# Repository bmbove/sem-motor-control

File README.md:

# sem-motor-control
See: https://github.com/OSUShellEcoMarathon

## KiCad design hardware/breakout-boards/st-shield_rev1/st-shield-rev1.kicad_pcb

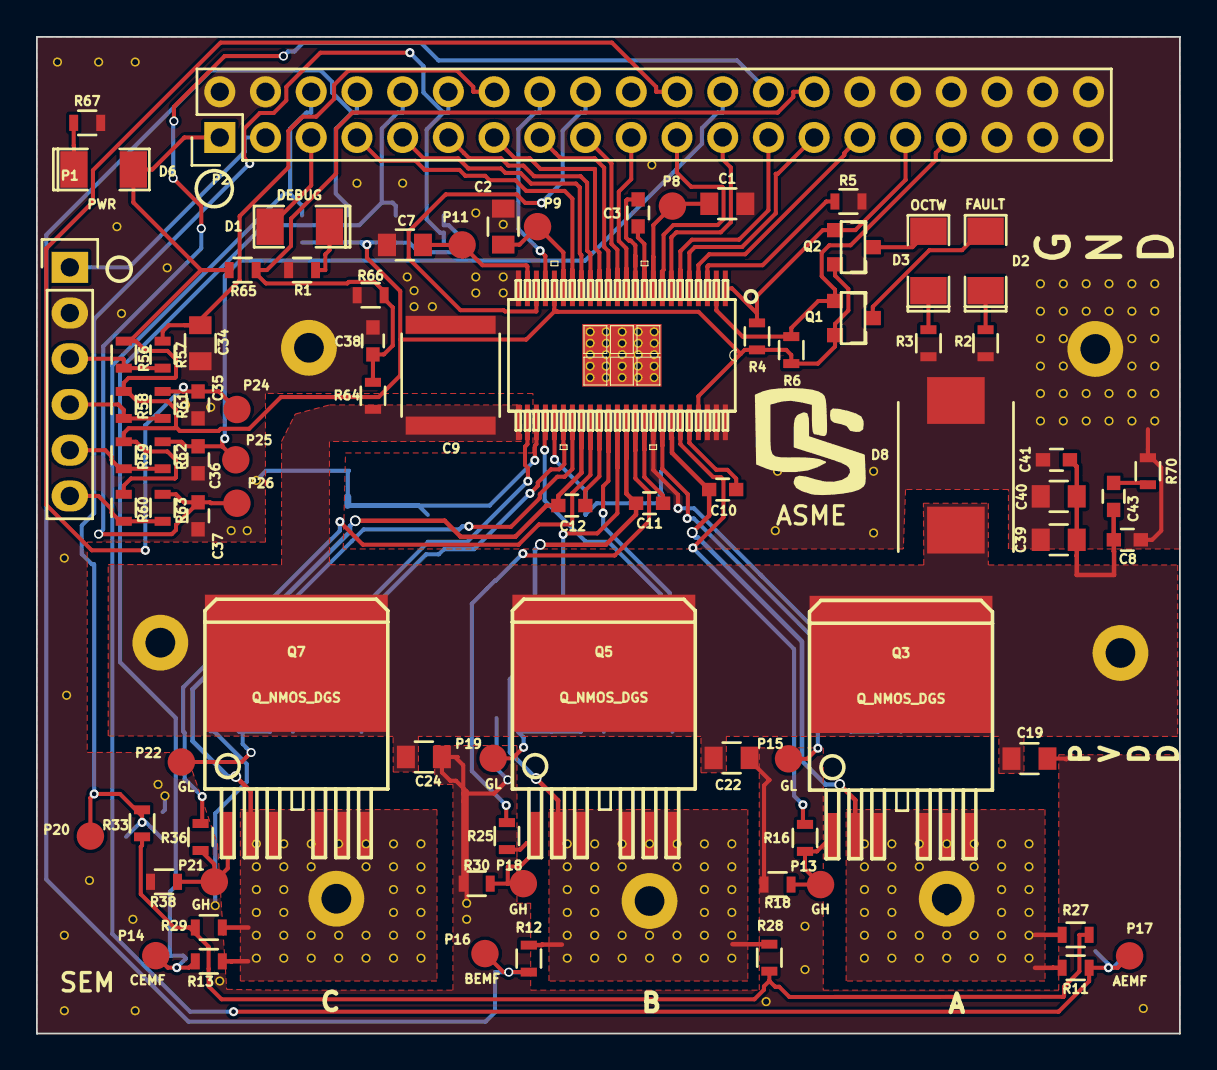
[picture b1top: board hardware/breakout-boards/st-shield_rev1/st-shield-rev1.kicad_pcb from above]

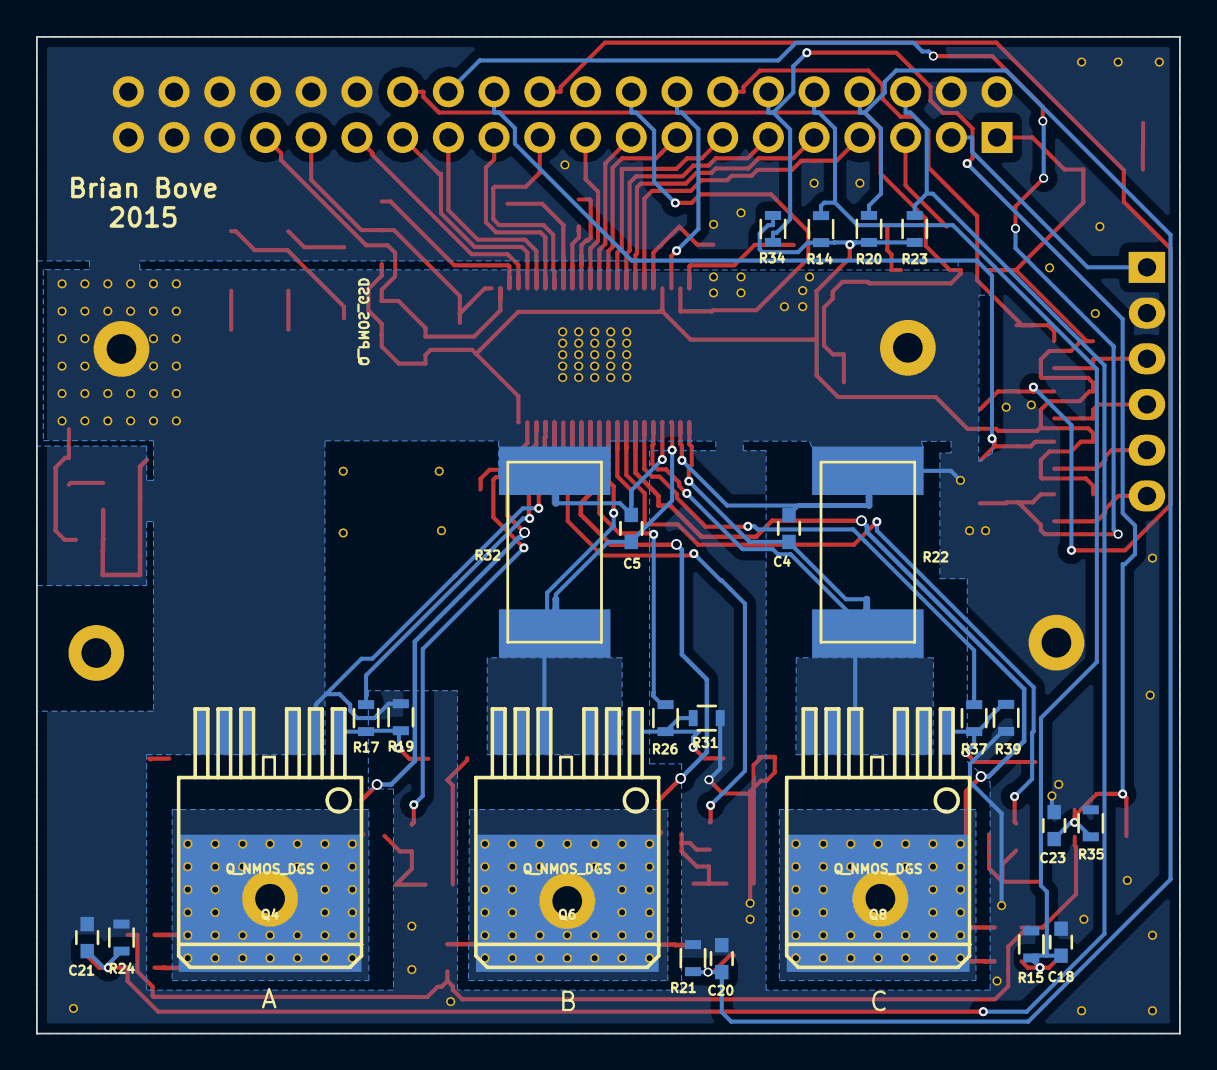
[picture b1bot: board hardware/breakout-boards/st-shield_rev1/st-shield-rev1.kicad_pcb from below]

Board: 2 copper layers, 63.5 x 55.4 mm, 327 parts (29 on the bottom side), 72 nets.

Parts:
C1, C19, C22, C24, C34, C39: 2.2u; C_0805
C2, C7, C40: 1u; C_0805
C3: .022u; C_0603
C4, C5: 1000p; C_0603
C8, C10, C11, C12, C38, C41: .1u; C_0603
C9: 4.7u; C_2220
C18, C20, C21, C23: .001u; C_0603
C35, C36, C37: 100p; C_0603
C43: .01u; C_0603
D1: LED; SMD-1206_Pol
D2: RED; SMD-1206_Pol
D3: YELLOW; SMD-1206_Pol
D6: GREEN; SMD-1206_Pol
D8: TVS; Diode-DO-214AB
MA: hack-via
MB: hack-via
MC: hack-via
P1: CONN_01X06; Pin_Header_Straight_1x06
P2: CONN_02X20; Pin_Header_Straight_2x20
P8, P9, P11, P13, P14, P15, P16, P17, P18, P19, P20, P21, P22, P24, P25, P26: TST; Measurement_Point_Round-SMD-Pad_Small
Q1, Q2: Q_PMOS_GSD; SparkFun-SOT23-3
Q3, Q4, Q5, Q6, Q7, Q8: Q_NMOS_DGS; D2PAK-7
R1, R2, R3, R67: 100; R_0603
R4, R6: 10k; R_0603
R5: 150k; R_0603
R11, R12, R13, R33, R64: 82.5k; R_0603
R14, R20, R23, R34, R65: 30.1k; R_0603
R15, R21, R24, R35, R66: 4.75k; R_0603
R16, R17, R25, R26, R36, R37: 10; R_0603
R18, R19, R30, R31, R38, R39: 47k; R_0603
R22, R32: .0003; WSL3921
R27, R28, R29: 34k; R_0603
R56, R58, R59, R60: 22k; R_0603
R57, R61, R62, R63: 1.6k; R_0603
R70: 3.3; R_0603
U11: DRV8303_DCA_48_SINGLE; drv8303-DCA48_4P42X3P48-M
V1, V2, V3, V4, V111111111, V111111111#2, V111111111#3, V111111111#4, V111111111#5, V111111111#6, V111111111#7, V111111111#8, V111111111#9, V111111111#10, V111111111#11, V111111111#12, V111111111#13, V111111111#14, V111111111#15, V111111111#16, V111111111#17, V111111111#18, V111111111#19, V111111111#20, V111111111#21, V111111111#22, V111111111#23, V111111111#24, V111111111#25, V111111111#26, V111111111#27, V111111111#28, V111111111#29, V111111111#30, V111111111#31, V111111111#32, V111111111#33, V111111111#34, V111111111#35, V111111111#36, V111111111#37, V111111111#38, V111111111#39, V111111111#40, V111111111#41, V111111111#42, V111111111#43, V111111111#44, V111111111#45, V111111111#46, V111111112, V111111113, V111111114, V111111115, V111111121, V111111122, V111111123, V111111124, V111111125, V111111131, V111111132, V111111133, V111111134, V111111135, V111111141, V111111142, V111111143, V111111144, V111111145, V111111151, V111111152, V111111153, V111111154, V111111155, V111111111111, V111111111112, V111111111113, V111111111114, V111111111115, V111111111116, V111111111121, V111111111122, V111111111123, V111111111124, V111111111125, V111111111126, V111111111131, V111111111132, V111111111135, V111111111136, V111111111141, V111111111145, V111111111146, V111111111151, V111111111152, V111111111155, V111111111156, V111111111161, V111111111162, V111111111163, V111111111164, V111111111165, V111111111166, V111111111171, V111111111172, V111111111173, V111111111174, V111111111175, V111111111176, V1111111111111, V1111111111112, V1111111111113, V1111111111114, V1111111111115, V1111111111116, V1111111111121, V1111111111122, V1111111111123, V1111111111124, V1111111111125, V1111111111126, V1111111111131, V1111111111132, V1111111111135, V1111111111136, V1111111111141, V1111111111145, V1111111111146, V1111111111151, V1111111111152, V1111111111155, V1111111111156, V1111111111161, V1111111111162, V1111111111163, V1111111111164, V1111111111165, V1111111111166, V1111111111171, V1111111111172, V1111111111173, V1111111111174, V1111111111175, V1111111111176, V11111111111111, V11111111111112, V11111111111113, V11111111111114, V11111111111115, V11111111111116, V11111111111121, V11111111111122, V11111111111123, V11111111111124, V11111111111125, V11111111111126, V11111111111131, V11111111111132, V11111111111135, V11111111111136, V11111111111141, V11111111111143, V11111111111144, V11111111111145, V11111111111146, V11111111111151, V11111111111152, V11111111111155, V11111111111156, V11111111111161, V11111111111162, V11111111111163, V11111111111164, V11111111111165, V11111111111166, V11111111111171, V11111111111172, V11111111111173, V11111111111174, V11111111111175, V11111111111176, V1111111111111111, V1111111111111112, V1111111111111113, V1111111111111114, V1111111111111115, V1111111111111116, V1111111111111121, V1111111111111122, V1111111111111123, V1111111111111124, V1111111111111125, V1111111111111126, V1111111111111131, V1111111111111132, V1111111111111135, V1111111111111136, V1111111111111141, V1111111111111142, V1111111111111145, V1111111111111146, V1111111111111151, V1111111111111152, V1111111111111153, V1111111111111154, V1111111111111155, V1111111111111156, V1111111111111161, V1111111111111162, V1111111111111163, V1111111111111164, V1111111111111165, V1111111111111166: hack-via
W1, W2, W3, W4: NET-TIE; nettie

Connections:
3V3: D6.2, P2.1, Q1.2, Q2.2, R4.1, R6.1, R14.1, R20.1, R23.1, R34.1, R56.1, R58.1, R59.1, R60.1, R65.1, U11.20, U11.45
5V: P1.1, P2.3
/FET Driver/DC_CAL: P2.21, U11.8
/FET Driver/EN: P2.19, U11.12
/FET Driver/FAULT: P2.33, Q1.1, R6.2, U11.2
/FET Driver/INH_A: P2.17, U11.13
/FET Driver/INH_B: P2.13, U11.15
/FET Driver/INH_C: P2.9, U11.17
/FET Driver/INL_A: P2.15, U11.14
/FET Driver/INL_B: P2.11, U11.16
/FET Driver/INL_C: P2.7, U11.18
/FET Driver/OCTW: P2.31, Q2.1, R4.2, U11.1
/FET Driver/SCLK: P2.23, U11.7
/FET Driver/SCS: P2.29, U11.4
/FET Driver/SDI: P2.27, U11.5
/FET Driver/SDO: P2.25, U11.6
/FET Driver/SL_B: Q6.3, R32.2, U11.35, W3.1
/FET Driver/SL_C: Q8.3, R22.2, U11.30, W1.1
/FET Driver/SO1: P2.16, U11.21
/FET Driver/SO2: P2.18, U11.22
/Hall Effect Sensor Filters/HALL_A_IN: P1.4, R58.2, R61.2
/Hall Effect Sensor Filters/HALL_A_OUT: C35.1, P2.22, P24.1, R61.1
/Hall Effect Sensor Filters/HALL_B_IN: P1.5, R59.2, R62.2
/Hall Effect Sensor Filters/HALL_B_OUT: C36.1, P2.24, P25.1, R62.1
/Hall Effect Sensor Filters/HALL_C_IN: P1.6, R60.2, R63.2
/Hall Effect Sensor Filters/HALL_C_OUT: C37.1, P2.26, P26.1, R63.1
/LED_D: D1.2, P2.5
/MOSFET Array/AEMF: C21.1, P2.6, P17.1, R11.1, R23.2, R24.1
/MOSFET Array/A_HI: R16.2, U11.43
/MOSFET Array/A_LO: R17.2, U11.41
/MOSFET Array/BEMF: C20.1, P2.8, P16.1, R12.1, R20.2, R21.1
/MOSFET Array/B_HI: R25.2, U11.38
/MOSFET Array/B_LO: R26.2, U11.36
/MOSFET Array/CEMF: C18.1, P2.10, P14.1, R13.1, R14.2, R15.1
/MOSFET Array/CUR_BN: C5.2, U11.29, W4.2
/MOSFET Array/CUR_BP: C5.1, U11.28, W3.2
/MOSFET Array/CUR_CN: C4.2, U11.27, W2.2
/MOSFET Array/CUR_CP: C4.1, U11.26, W1.2
/MOSFET Array/C_HI: R36.2, U11.33
/MOSFET Array/C_LO: R37.2, U11.31
/MOSFET Array/MOTOR_A: C10.2, Q3.3, Q4.1, R11.2, R27.2, U11.42, V11111111111111.1, V11111111111112.1, V11111111111113.1, V11111111111114.1, V11111111111115.1, V11111111111116.1, V11111111111121.1, V11111111111122.1, V11111111111123.1, V11111111111124.1, V11111111111125.1, V11111111111126.1, V11111111111131.1, V11111111111132.1, V11111111111135.1, V11111111111136.1, V11111111111141.1, V11111111111143.1, V11111111111144.1, V11111111111145.1, V11111111111146.1, V11111111111151.1, V11111111111152.1, V11111111111155.1, V11111111111156.1, V11111111111161.1, V11111111111162.1, V11111111111163.1, V11111111111164.1, V11111111111165.1, V11111111111166.1, V11111111111171.1, V11111111111172.1, V11111111111173.1, V11111111111174.1, V11111111111175.1, V11111111111176.1
/MOSFET Array/MOTOR_B: C11.2, Q5.3, Q6.1, R12.2, R28.2, U11.37, V1111111111111.1, V1111111111112.1, V1111111111113.1, V1111111111114.1, V1111111111115.1, V1111111111116.1, V1111111111121.1, V1111111111122.1, V1111111111123.1, V1111111111124.1, V1111111111125.1, V1111111111126.1, V1111111111131.1, V1111111111132.1, V1111111111135.1, V1111111111136.1, V1111111111141.1, V1111111111145.1, V1111111111146.1, V1111111111151.1, V1111111111152.1, V1111111111155.1, V1111111111156.1, V1111111111161.1, V1111111111162.1, V1111111111163.1, V1111111111164.1, V1111111111165.1, V1111111111166.1, V1111111111171.1, V1111111111172.1, V1111111111173.1, V1111111111174.1, V1111111111175.1, V1111111111176.1
/MOSFET Array/MOTOR_C: C12.2, Q7.3, Q8.1, R13.2, R29.2, U11.32, V111111111111.1, V111111111112.1, V111111111113.1, V111111111114.1, V111111111115.1, V111111111116.1, V111111111121.1, V111111111122.1, V111111111123.1, V111111111124.1, V111111111125.1, V111111111126.1, V111111111131.1, V111111111132.1, V111111111135.1, V111111111136.1, V111111111141.1, V111111111145.1, V111111111146.1, V111111111151.1, V111111111152.1, V111111111155.1, V111111111156.1, V111111111161.1, V111111111162.1, V111111111163.1, V111111111164.1, V111111111165.1, V111111111166.1, V111111111171.1, V111111111172.1, V111111111173.1, V111111111174.1, V111111111175.1, V111111111176.1
/MOSFET Array/MOTOR_N: C23.1, P2.12, P20.1, R33.1, R34.2, R35.1
/Power Management/DC_IN: C38.1, P2.28, R64.1, R65.2, R66.1
/Temperature Sensors/T0: C34.1, P2.14, R57.1
/Temperature Sensors/T_MOTOR: P1.3, R56.2, R57.2
GND: C1.2, C2.2, C7.2, C8.2, C9.2, C18.2, C19.2, C20.2, C21.2, C22.2, C23.2, C24.2, C34.2, C35.2, C36.2, C37.2, C38.2, C39.2, C40.2, C41.2, D8.2, P1.2, P2.2, P2.4, P2.30, P2.32, P2.34, P2.35, P2.36, P2.37, P2.38, P2.39, P2.40, Q4.3, R1.2, R2.2, R3.2, R5.2, R15.2, R18.1, R19.1, R21.2, R22.1, R24.2, R30.1, R31.1, R32.1, R35.2, R38.1, R39.1, R66.2, R67.2, R70.2, U11.24, U11.40, U11.46, U11.47, U11.48, V111111111.1, V111111111#2.1, V111111111#3.1, V111111111#4.1, V111111111#5.1, V111111111#6.1, V111111111#7.1, V111111111#8.1, V111111111#9.1, V111111111#10.1, V111111111#11.1, V111111111#12.1, V111111111#13.1, V111111111#14.1, V111111111#15.1, V111111111#16.1, V111111111#17.1, V111111111#18.1, V111111111#19.1, V111111111#20.1, V111111111#21.1, V111111111#22.1, V111111111#23.1, V111111111#24.1, V111111111#25.1, V111111111#26.1, V111111111#27.1, V111111111#28.1, V111111111#29.1, V111111111#30.1, V111111111#31.1, V111111111#32.1, V111111111#33.1, V111111111#34.1, V111111111#35.1, V111111111#36.1, V111111111#37.1, V111111111#38.1, V111111111#39.1, V111111111#40.1, V111111111#41.1, V111111111#42.1, V111111111#43.1, V111111111#44.1, V111111111#45.1, V111111111#46.1, V111111112.1, V111111113.1, V111111114.1, V111111115.1, V111111121.1, V111111122.1, V111111123.1, V111111124.1, V111111125.1, V111111131.1, V111111132.1, V111111133.1, V111111134.1, V111111135.1, V111111141.1, V111111142.1, V111111143.1, V111111144.1, V111111145.1, V111111151.1, V111111152.1, V111111153.1, V111111154.1, V111111155.1, V1111111111111111.1, V1111111111111112.1, V1111111111111113.1, V1111111111111114.1, V1111111111111115.1, V1111111111111116.1, V1111111111111121.1, V1111111111111122.1, V1111111111111123.1, V1111111111111124.1, V1111111111111125.1, V1111111111111126.1, V1111111111111131.1, V1111111111111132.1, V1111111111111135.1, V1111111111111136.1, V1111111111111141.1, V1111111111111142.1, V1111111111111145.1, V1111111111111146.1, V1111111111111151.1, V1111111111111152.1, V1111111111111153.1, V1111111111111154.1, V1111111111111155.1, V1111111111111156.1, V1111111111111161.1, V1111111111111162.1, V1111111111111163.1, V1111111111111164.1, V1111111111111165.1, V1111111111111166.1, W2.1, W4.1
unnamed: C1.1, P8.1, U11.9
unnamed: C2.1, P9.1, U11.19
unnamed: C3.1, U11.10
unnamed: C3.2, U11.11
unnamed: C7.1, P11.1, U11.23
unnamed: C10.1, U11.44
unnamed: C11.1, U11.39
unnamed: C12.1, U11.34
unnamed: C43.2, R70.1
unnamed: D1.1, R1.1
unnamed: D2.1, R2.1
unnamed: D2.2, Q1.3
unnamed: D3.1, R3.1
unnamed: D3.2, Q2.3
unnamed: D6.1, R67.1
unnamed: P13.1, Q3.2, R16.1, R18.2
unnamed: P15.1, Q4.2, R17.1, R19.2
unnamed: P18.1, Q5.2, R25.1, R30.2
unnamed: P19.1, Q6.2, R26.1, R31.2
unnamed: P21.1, Q7.2, R36.1, R38.2
unnamed: P22.1, Q8.2, R37.1, R39.2
unnamed: R5.1, U11.3
unnamed: R27.1, R28.1, R29.1, R33.2
PVDD: C8.1, C9.1, C19.1, C22.1, C24.1, C39.1, C40.1, C41.1, C43.1, D8.1, Q3.1, Q5.1, Q7.1, R64.2, U11.25

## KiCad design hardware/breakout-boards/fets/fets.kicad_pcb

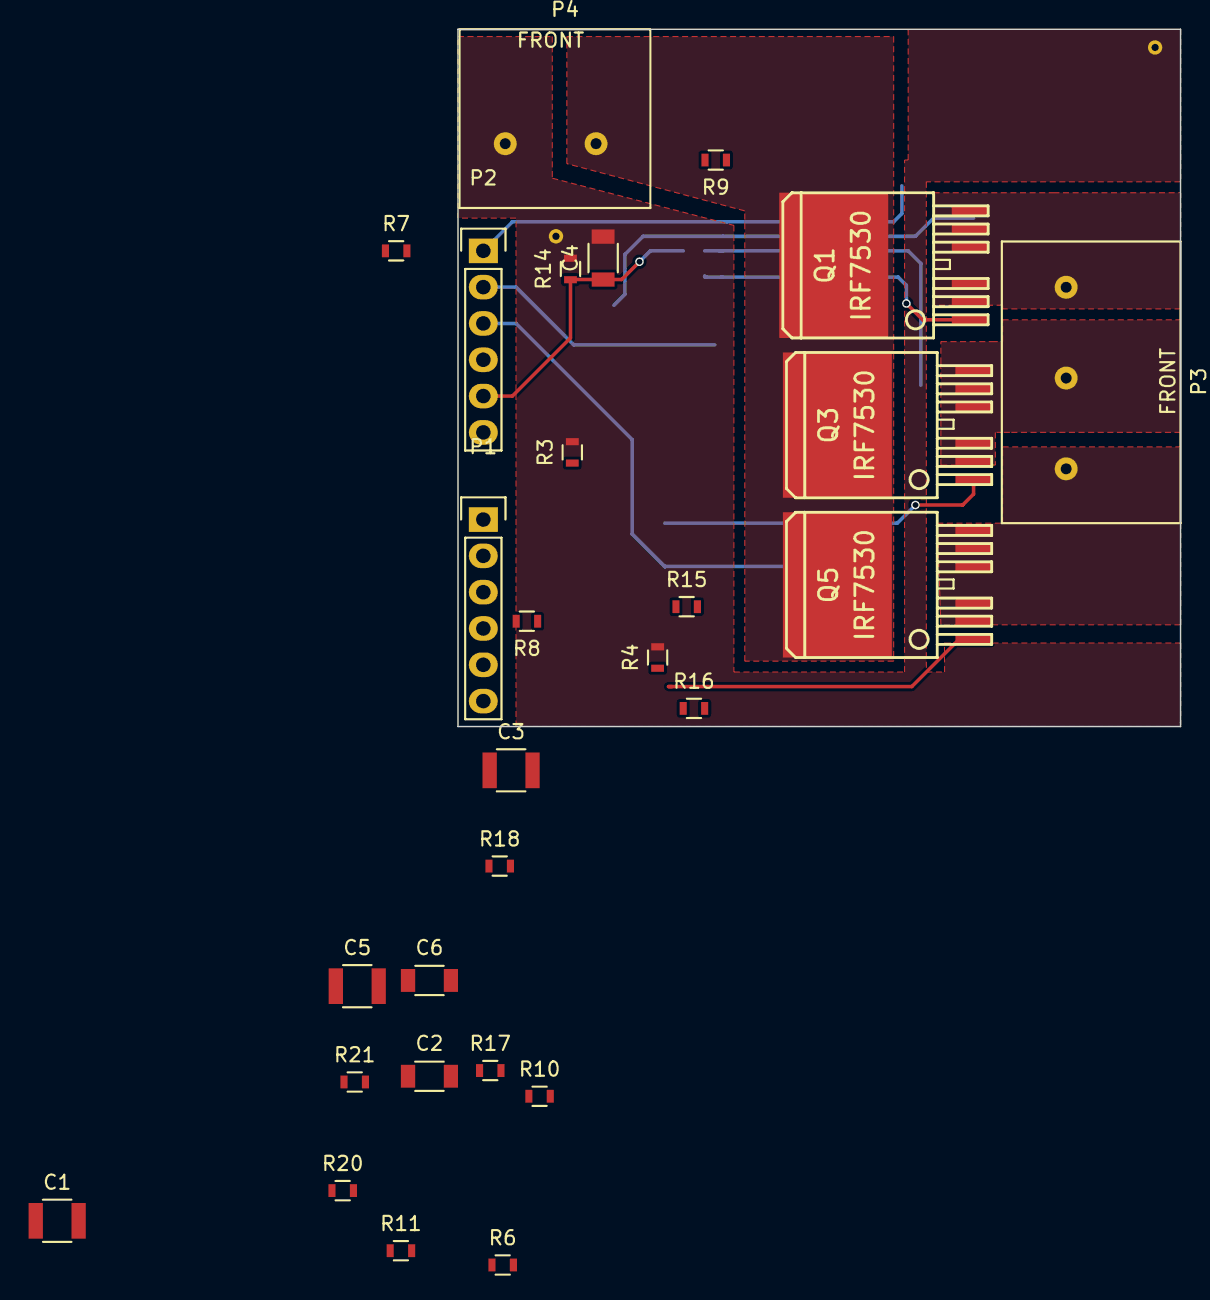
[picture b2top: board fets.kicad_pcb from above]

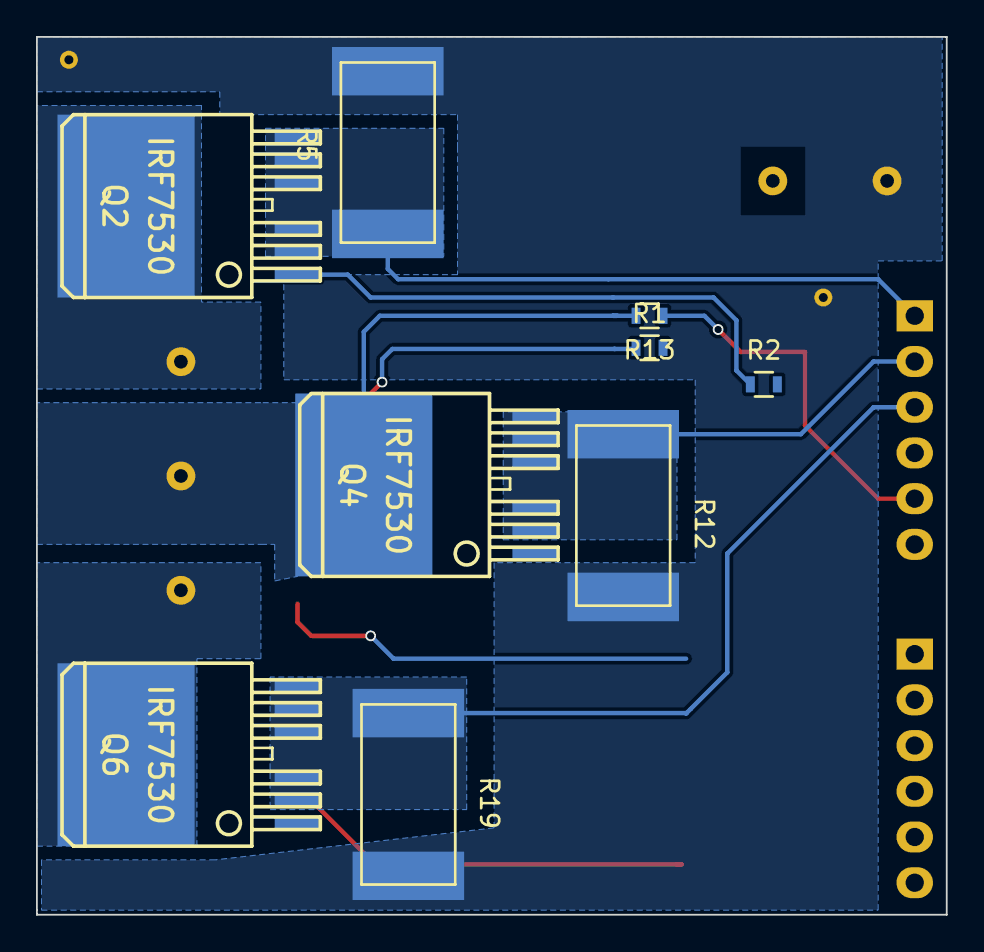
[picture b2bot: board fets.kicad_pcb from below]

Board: 2 copper layers, 50.5 x 48.8 mm, 37 parts (9 on the bottom side), 23 nets.

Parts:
C1, C3, C5: 2.2u; C_1210
C2, C4, C6: .1u; C_1206
P1, P2: CONN_01X06; Pin_Header_Straight_1x06
P3: CONN_01X03; OSTT7030150
P4: CONN_01X02; OSTT7020150
Q1, Q2, Q3, Q4, Q5, Q6: IRF7530; D2PAK-7
R1, R2, R8, R9, R15, R16: 10; R_0603
R3, R4, R10, R11, R17, R18: 10K; R_0603
R5, R12, R19: WSL3921
R6, R13, R20: 95.3k; R_0603
R7, R14, R21: 4.99k; R_0603

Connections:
48V: C1.1, C3.1, C5.1, P4.1, Q1.4, Q3.4, Q5.4
A_CUR: P2.1, Q2.2, Q2.3, Q2.5, Q2.6, Q2.7, R5.1
A_EMF: C2.1, P2.4, R6.1, R7.1
A_HI: P1.1, R1.2
A_LO: P1.2, R2.2
B_CUR: P2.2, Q4.2, Q4.3, Q4.5, Q4.6, Q4.7, R12.1
B_EMF: C4.1, P2.5, R13.1, R14.1
B_HI: P1.3, R8.2
B_LO: P1.4, R9.2
C_CUR: P2.3, Q6.2, Q6.3, Q6.5, Q6.6, Q6.7, R19.1
C_EMF: C6.1, P2.6, R20.1, R21.1
C_HI: P1.5, R15.2
C_LO: P1.6, R16.2
GND: C1.2, C2.2, C3.2, C4.2, C5.2, C6.2, P4.2, R3.2, R4.2, R5.2, R7.2, R10.2, R11.2, R12.2, R14.2, R17.2, R18.2, R19.2, R21.2
MOTOR_A: P3.3, Q1.2, Q1.3, Q1.5, Q1.6, Q1.7, Q2.4, R6.2
MOTOR_B: P3.2, Q3.2, Q3.3, Q3.5, Q3.6, Q3.7, Q4.4, R13.2
MOTOR_C: P3.1, Q5.2, Q5.3, Q5.5, Q5.6, Q5.7, Q6.4, R20.2
unnamed: Q1.1, R1.1, R3.1
unnamed: Q2.1, R2.1, R4.1
unnamed: Q3.1, R8.1, R10.1
unnamed: Q4.1, R9.1, R11.1
unnamed: Q5.1, R15.1, R17.1
unnamed: Q6.1, R16.1, R18.1

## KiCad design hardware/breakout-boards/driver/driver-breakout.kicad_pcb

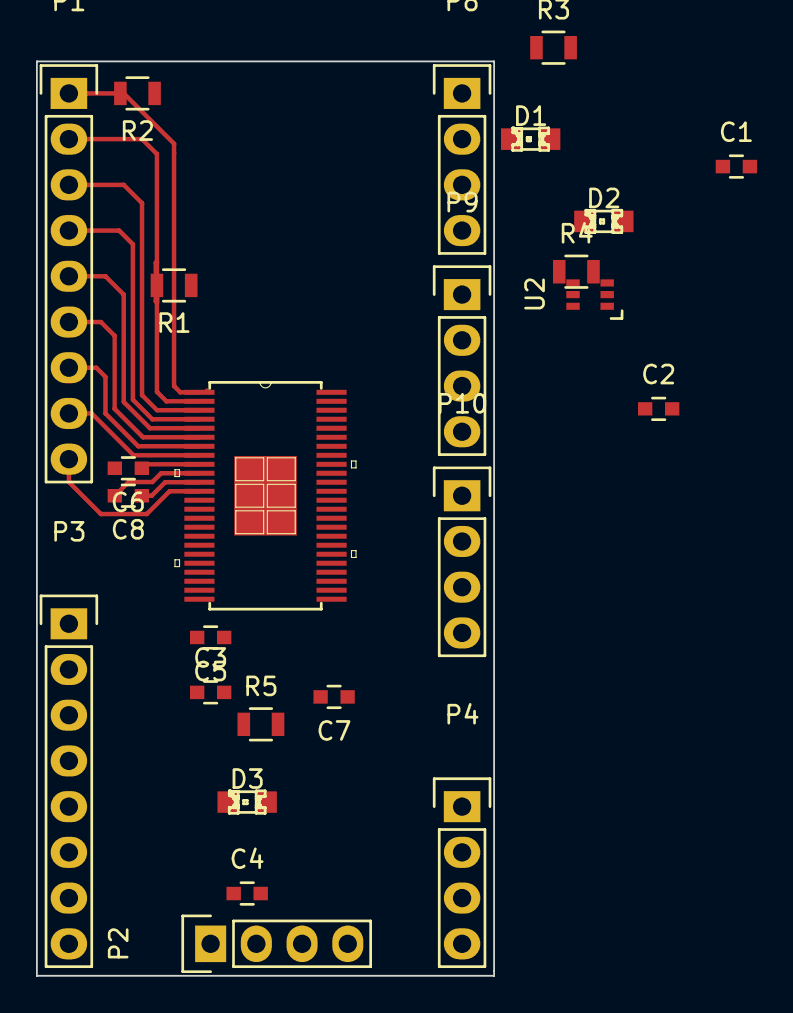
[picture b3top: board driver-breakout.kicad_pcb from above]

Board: 2 copper layers, 25.4 x 50.8 mm, 25 parts (0 on the bottom side), 49 nets.

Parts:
C1, C2, C3: .1u; C_0603
C4, C5: 1u; C_0603
C6: 2.2u; C_0603
C7: 4.7u; C_0603
C8: 22n; C_0603
D1, D2, D3: LED; LED-0805
P1: CONN_01X09; Pin_Header_Straight_1x09
P2, P4, P8, P9, P10: CONN_01X04; Pin_Header_Straight_1x04
P3: CONN_01X08; Pin_Header_Straight_1x08
R1, R2: 10k; R_0805
R3, R4, R5: 100; R_0805
U1: DRV8303_DCA_48; drv8303-DCA48_4P42X3P48
U2: DUAL_PMOS; SC-70-6

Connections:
3V3: D3.2, P2.1, R1.1, R2.1, U1.20, U1.45, U2.1, U2.4
48V: C7.1, P2.2, U1.25
/BST_A: C1.2, U1.44
/BST_B: C2.2, U1.39
/BST_C: C3.2, U1.34
/CLK: P1.7, U1.7
/CS: P1.4, U1.4
/DC_CAL: P1.8, U1.8
/DTC: P1.3, U1.3
/EN: P1.9, U1.12
/FAULT: P1.2, R1.2, U1.2, U2.5
/GH_A: P8.1, U1.43
/GH_B: P9.1, U1.38
/GH_C: P10.1, U1.33
/GL_A: P8.3, U1.41
/GL_B: P9.3, U1.36
/GL_C: P10.3, U1.31
/INH_A: P3.1, U1.13
/INH_B: P3.3, U1.15
/INH_C: P3.5, U1.17
/INL_A: P3.2, U1.14
/INL_B: P3.4, U1.16
/INL_C: P3.6, U1.18
/OCTW: P1.1, R2.2, U1.1, U2.2
/SDI: P1.5, U1.5
/SDO: P1.6, U1.6
/SH_A: C1.1, P8.2, U1.42
/SH_B: C2.1, P9.2, U1.37
/SH_C: C3.1, P10.2, U1.32
/SL_A: P8.4, U1.40
/SL_B: P9.4, U1.35
/SL_C: P10.4, U1.30
/SN1: P4.1, U1.29
/SN2: P4.3, U1.27
/SO1: P3.7, U1.21
/SO2: P3.8, U1.22
/SP1: P4.2, U1.28
/SP2: P4.4, U1.26
GND: C4.2, C5.2, C6.2, C7.2, P2.3, P2.4, R3.2, R4.2, R5.2, U1.24, U1.46, U1.47, U1.48, U1.49
unnamed: C4.1, U1.23
unnamed: C5.1, U1.19
unnamed: C6.1, U1.9
unnamed: C8.1, U1.11
unnamed: C8.2, U1.10
unnamed: D1.1, R3.1
unnamed: D1.2, U2.3
unnamed: D2.1, R4.1
unnamed: D2.2, U2.6
unnamed: D3.1, R5.1

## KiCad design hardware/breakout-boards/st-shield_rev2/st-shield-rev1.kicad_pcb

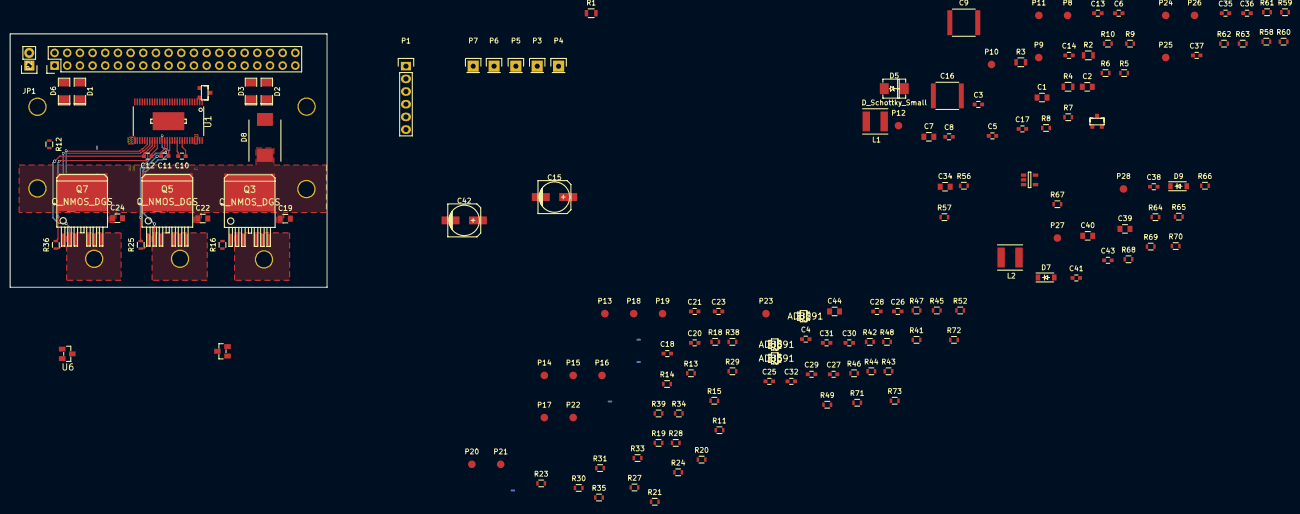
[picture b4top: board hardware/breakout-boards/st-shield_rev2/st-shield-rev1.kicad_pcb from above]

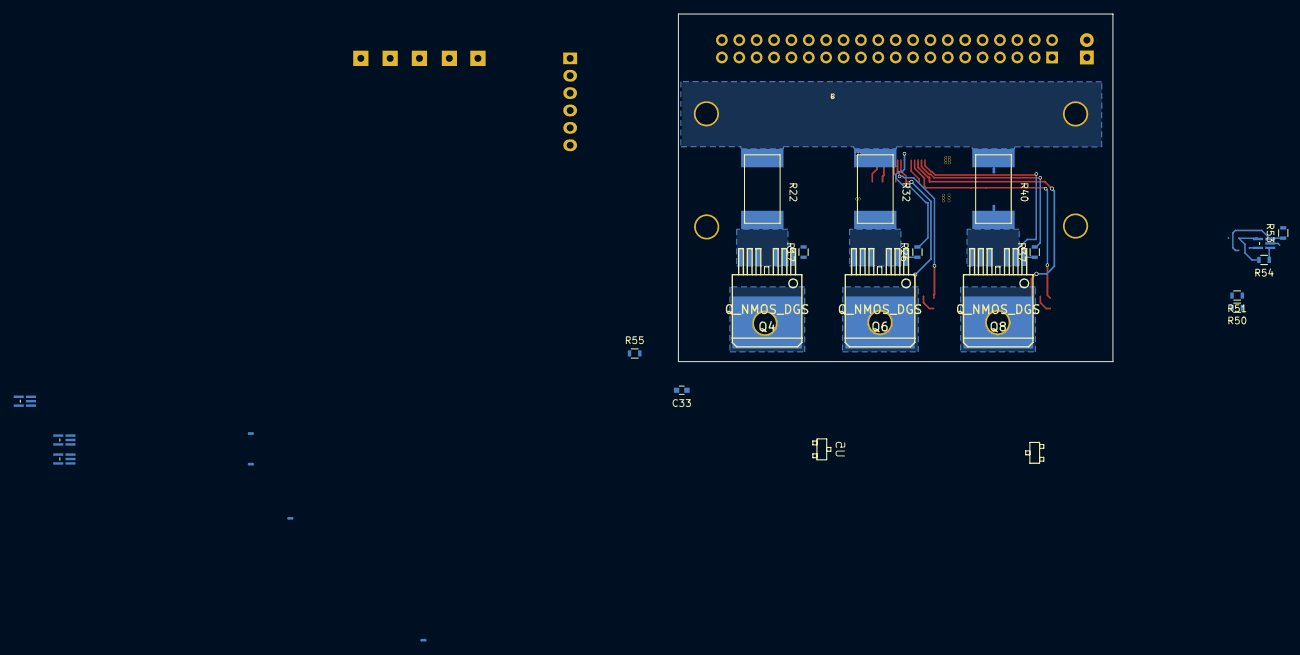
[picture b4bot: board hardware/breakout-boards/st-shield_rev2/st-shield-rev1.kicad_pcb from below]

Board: 4 copper layers, 63.5 x 50.8 mm, 178 parts (25 on the bottom side), 100 nets.

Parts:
C1, C19, C22, C24, C34, C39, C44: 2.2u; C_0805
C2, C7, C40: 1u; C_0805
C3: .022u; C_0603
C4, C8, C10, C11, C12, C13, C14, C26, C29, C32, C38, C41: .1u; C_0603
C5: 6800p; C_0603
C6: 120p; C_0603
C9, C16: 10u; C_2220
C15, C42: 100u; c_elec_6.3x7.7
C17: .015u; C_0603
C18, C20, C21, C23, C25, C27, C30: .001u; C_0603
C28, C31, C33, C35, C36, C37: 100p; C_0603
C43: .01u; C_0603
D1: LED; SMD-1206_Pol
D2: RED; SMD-1206_Pol
D3: YELLOW; SMD-1206_Pol
D5: D_Schottky_Small; DO-214AA(SMB)
D6: GREEN; SMD-1206_Pol
D7: 3.3 Vbkdn; SOD-123
D8: TVS; Diode-DO-214AB
D9: 5Vbkdn; SOD-123
JP1: JUMPER; Pin_Header_Straight_1x02
L1: 22u; SMD_inductor_5x4mm
L2: 2.2u; SMD_inductor_5x4mm
P1: CONN_01X06; Pin_Header_Straight_1x06
P2: CONN_02X20; Pin_Header_Straight_2x20
P3: CH_A; Pin_Header_Straight_1x01
P4: CH_B; Pin_Header_Straight_1x01
P5: CH_C; Pin_Header_Straight_1x01
P6: PVDD; Pin_Header_Straight_1x01
P7: GND; Pin_Header_Straight_1x01
P8, P9, P10, P11, P12, P13, P14, P15, P16, P17, P18, P19, P20, P21, P22, P23, P24, P25, P26, P27, P28: TST; Measurement_Point_Round-SMD-Pad_Small
Q1, Q2: Q_PMOS_GSD; SparkFun-SOT23-3
Q3, Q4, Q5, Q6, Q7, Q8: Q_NMOS_DGS; D2PAK-7
R1, R2, R3: 100; R_0805
R4: 10k; R_0805
R5: 150k; R_0603
R6: 10k; R_0603
R7: 118k; R_0603
R8: 22.1k; R_0603
R9: 16.2k; R_0603
R10: 220k; R_0603
R11, R12, R13, R33, R64, R71, R72: 82.5k; R_0603
R14, R20, R23, R34, R65: 30.1k; R_0603
R15, R21, R24, R35, R66: 4.75k; R_0603
R16, R17, R25, R26, R36, R37: 10; R_0603
R18, R19, R30, R31, R38, R39: 47k; R_0603
R22, R32, R40: .0003; WSL3921
R27, R28, R29: 34k; R_0603
R41, R42, R46, R47, R50, R51: 1k; R_0603
R43, R44, R48, R49, R53, R54: 20k; R_0603
R45, R52, R55: 1.62k; R_0603
R56, R58, R59, R60: 22k; R_0603
R57, R61, R62, R63: 1.6k; R_0603
R67, R73: 100; R_0603
R68: 274k; R_0603
R69: 60.4k; R_0603
R70: 3.3; R_0603
U1: DRV8301_DCA_56; -DCA56_6P35X3P61-M
U2, U3, U4, U8: AD8691; -KS_5
U5, U6: MCP9700-X_TT; -SOT-23_MC
U7: TLV62565DBVR; -DBV0005A
W1, W2, W3, W4, W5, W6: NET-TIE; nettie

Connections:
1V65: C44.1, P23.1, R43.2, R48.2, R53.2, R73.1
3V3: C4.1, C26.1, C29.1, C32.1, C42.1, D6.2, D7.1, JP1.1, L2.2, P28.1, Q1.2, Q2.2, R4.1, R6.1, R14.1, R20.1, R23.1, R34.1, R56.1, R58.1, R59.1, R60.1, R65.1, R68.1, R71.2, U1.24, U1.49, U2.5, U3.5, U4.5, U5.1, U6.1, U8.5
5V: C15.1, D9.1, L1.2, P1.1, P12.1, R7.1, U7.1, U7.4
/FET Driver/DC_CAL: P2.21, U1.12
/FET Driver/EN: P2.19, U1.16
/FET Driver/FAULT: P2.33, Q1.1, R6.2, U1.6
/FET Driver/INH_A: P2.17, U1.17
/FET Driver/INH_B: P2.13, U1.19
/FET Driver/INH_C: P2.9, U1.21
/FET Driver/INL_A: P2.15, U1.18
/FET Driver/INL_B: P2.11, U1.20
/FET Driver/INL_C: P2.7, U1.22
/FET Driver/OCTW: P2.31, Q2.1, R4.2, U1.5
/FET Driver/SCLK: P2.23, U1.11
/FET Driver/SCS: P2.29, U1.8
/FET Driver/SDI: P2.27, U1.9
/FET Driver/SDO: P2.25, U1.10
/FET Driver/SL_A: Q4.3, R22.2, U1.44, W1.1
/FET Driver/SL_B: Q6.3, R32.2, U1.39, W3.1
/FET Driver/SL_C: Q8.3, R40.2, U1.34, W5.1
/Hall Effect Sensor Filters/HALL_A_IN: P1.4, R58.2, R61.2
/Hall Effect Sensor Filters/HALL_A_OUT: C35.1, P2.28, P24.1, R61.1
/Hall Effect Sensor Filters/HALL_B_IN: P1.5, R59.2, R62.2
/Hall Effect Sensor Filters/HALL_B_OUT: C36.1, P2.30, P25.1, R62.1
/Hall Effect Sensor Filters/HALL_C_IN: P1.6, R60.2, R63.2
/Hall Effect Sensor Filters/HALL_C_OUT: C37.1, P2.32, P26.1, R63.1
/LED_D: D1.2, P2.5
/MOSFET Array/AEMF: C21.1, P2.6, P17.1, R11.1, R23.2, R24.1
/MOSFET Array/A_HI: R16.2, U1.47
/MOSFET Array/A_LO: R17.2, U1.45
/MOSFET Array/BEMF: C20.1, P2.8, P16.1, R12.1, R20.2, R21.1
/MOSFET Array/B_HI: R25.2, U1.42
/MOSFET Array/B_LO: R26.2, U1.40
/MOSFET Array/CEMF: C18.1, P2.10, P14.1, R13.1, R14.2, R15.1
/MOSFET Array/CUR_AN: C25.2, R42.2, W2.2
/MOSFET Array/CUR_AP: C25.1, R41.2, W1.2
/MOSFET Array/CUR_BN: C27.2, R47.2, W4.2
/MOSFET Array/CUR_BP: C27.1, R46.2, W3.2
/MOSFET Array/CUR_CN: C30.2, R51.2, W6.2
/MOSFET Array/CUR_CP: C30.1, R50.2, W5.2
/MOSFET Array/C_HI: R36.2, U1.37
/MOSFET Array/C_LO: R37.2, U1.35
/MOSFET Array/MOTOR_A: C10.2, P3.1, Q3.3, Q4.1, R11.2, R27.2, U1.46
/MOSFET Array/MOTOR_B: C11.2, P4.1, Q5.3, Q6.1, R12.2, R28.2, U1.41
/MOSFET Array/MOTOR_C: C12.2, P5.1, Q7.3, Q8.1, R13.2, R29.2, U1.36
/MOSFET Array/MOTOR_N: C23.1, P2.12, R33.1, R34.2, R35.1
/Power Management/DC_IN: C38.1, P2.34, R64.1, R65.2, R66.1
/Shunt Amplifiers/IA: C28.1, P2.22, R45.1
/Shunt Amplifiers/IB: C31.1, P2.24, R52.1
/Shunt Amplifiers/IC: C33.1, P2.26, R55.1
/Temperature Sensors/T0: C34.1, P2.14, R57.1
/Temperature Sensors/T1: P2.16, U5.2
/Temperature Sensors/T2: P2.18, U6.2
/Temperature Sensors/T_MOTOR: P1.3, R56.2, R57.2
GND: C1.2, C2.2, C4.2, C5.2, C6.2, C7.2, C8.2, C9.2, C14.2, C15.2, C16.2, C17.2, C18.2, C19.2, C20.2, C21.2, C22.2, C23.2, C24.2, C26.2, C28.2, C29.2, C31.2, C32.2, C33.2, C34.2, C35.2, C36.2, C37.2, C38.2, C39.2, C40.2, C41.2, C42.2, C44.2, D5.2, D7.2, D8.2, D9.2, P1.2, P2.2, P2.4, P2.35, P2.36, P2.37, P2.38, P2.39, P2.40, P7.1, R1.2, R2.2, R3.2, R5.2, R8.2, R10.2, R15.2, R18.1, R19.1, R21.2, R22.1, R24.2, R30.1, R31.1, R32.1, R35.2, R38.1, R39.1, R40.1, R66.2, R67.2, R69.2, R70.2, R72.1, U1.28, U1.57, U2.2, U3.2, U4.2, U5.3, U6.3, U7.2, U8.2, W2.1, W4.1, W6.1
unnamed: C1.1, P8.1, U1.13
unnamed: C2.1, P9.1, U1.23
unnamed: C3.1, U1.14
unnamed: C3.2, U1.15
unnamed: C5.1, R9.2
unnamed: C6.1, R9.1, U1.2
unnamed: C7.1, P11.1, U1.27
unnamed: C10.1, U1.48
unnamed: C11.1, U1.43
unnamed: C12.1, U1.38
unnamed: C13.1, U1.52
unnamed: C13.2, D5.1, L1.1, U1.50, U1.51
unnamed: C17.1, U1.56
unnamed: C43.2, R70.1
unnamed: D1.1, R1.1
unnamed: D2.1, R2.1
unnamed: D2.2, Q1.3
unnamed: D3.1, R3.1
unnamed: D3.2, Q2.3
unnamed: D6.1, R67.1
unnamed: JP1.2, P2.1, P2.3
unnamed: L2.1, U7.3
unnamed: P10.1, R7.2, R8.1, U1.3
unnamed: P13.1, Q3.2, R16.1, R18.2
unnamed: P15.1, Q4.2, R17.1, R19.2
unnamed: P18.1, Q5.2, R25.1, R30.2
unnamed: P19.1, Q6.2, R26.1, R31.2
unnamed: P21.1, Q7.2, R36.1, R38.2
unnamed: P22.1, Q8.2, R37.1, R39.2
unnamed: R5.1, U1.7
unnamed: R10.1, U1.1
unnamed: R27.1, R28.1, R29.1, R33.2
unnamed: R41.1, R43.1, U2.3
unnamed: R42.1, R44.2, U2.4
unnamed: R44.1, R45.2, U2.1
unnamed: R46.1, R48.1, U3.3
unnamed: R47.1, R49.2, U3.4
unnamed: R49.1, R52.2, U3.1
unnamed: R50.1, R53.1, U4.3
unnamed: R51.1, R54.2, U4.4
unnamed: R54.1, R55.2, U4.1
unnamed: R68.2, R69.1, U7.5
unnamed: R71.1, R72.2, U8.3
unnamed: R73.2, U8.1, U8.4
PVDD: C8.1, C9.1, C14.1, C16.1, C19.1, C22.1, C24.1, C39.1, C40.1, C41.1, C43.1, D8.1, P6.1, P27.1, Q3.1, Q5.1, Q7.1, R64.2, U1.29, U1.53, U1.54

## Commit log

2015-07-22 folder reorganization
2015-07-24 Adds library for TI uc, start of uc schematic
2015-07-24 update plots
2015-07-25 basic uc parts. adds FTDI chip for serial programming
2015-07-25 adds reset circuit for ftdi->uc
2015-07-25 ftdi.sch: reworked buffer
2015-07-25 ftdi.sch: reworked buffer again. looks.. better.
2015-07-25 ftdi.sch: replace ttl with dual buffer chip, insert parts for usb side
2015-07-25 Added relevent datasheets
2015-07-25 adds datasheet for driver IC
2015-07-25 driver schematic added, libraries reworked a little
2015-07-27 adds ADG904 library
2015-07-27 Added ad8227 (inst amp) datasheet
2015-07-28 adds libraries for AD8227 inst. amp
2015-07-29 adds block diagram
2015-07-29 updated plots to include current amp
2015-07-29 rename schematic pdf
2015-08-02 adds breakout board for driver IC
2015-08-03 Add indicator leds to driver, LDO to FTDI chip
2015-08-03 current sense amp gain worked out, resistor values added for LEDs
2015-08-04 annotates everything, adds back-emf sensing
2015-08-13 adds FET breakout board project
2015-08-14 FET breakoutboard complete, generated gerbers and sent off to fab
2015-08-27 Update bemf sense config, current sense config
2015-09-16 adds driver breakout board + start of combined FET and driver shield
2015-09-25 adds driver and fet schematics for shield
2015-09-30 shield: update shunt notes and part
2015-09-30 shield: adds signal conditioning to back-emf lines
2015-10-02 st-shield: adds shunt amplifiers
2015-10-12 st-shield: replaces DRV8303 with DRV8301, requirements updated for 5V and 3.3V
2015-10-15 st-shield: adds pdu block
2015-10-18 st-shield: adds 40 pin connector
2015-10-19 st-shield: board layout started
2015-10-19 st-shield: more board work. maybe remove some op amps?
2015-10-21 shield: splits into rev1 and rev2
2015-10-21 st-shield-rev1: finished board layout. need to clean up (then send to fab)
2015-10-21 shield rev1: finalized routing, mounting holes, and silk screen refs. need to add logo
2015-10-22 st-shield-rev1: sent to fab
